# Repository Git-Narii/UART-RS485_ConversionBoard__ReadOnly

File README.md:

RS485からUARTに信号を変換するための基板

逆方向の変換は不可

双方向化Ver.  と通信方向自動制御Ver.は作成中

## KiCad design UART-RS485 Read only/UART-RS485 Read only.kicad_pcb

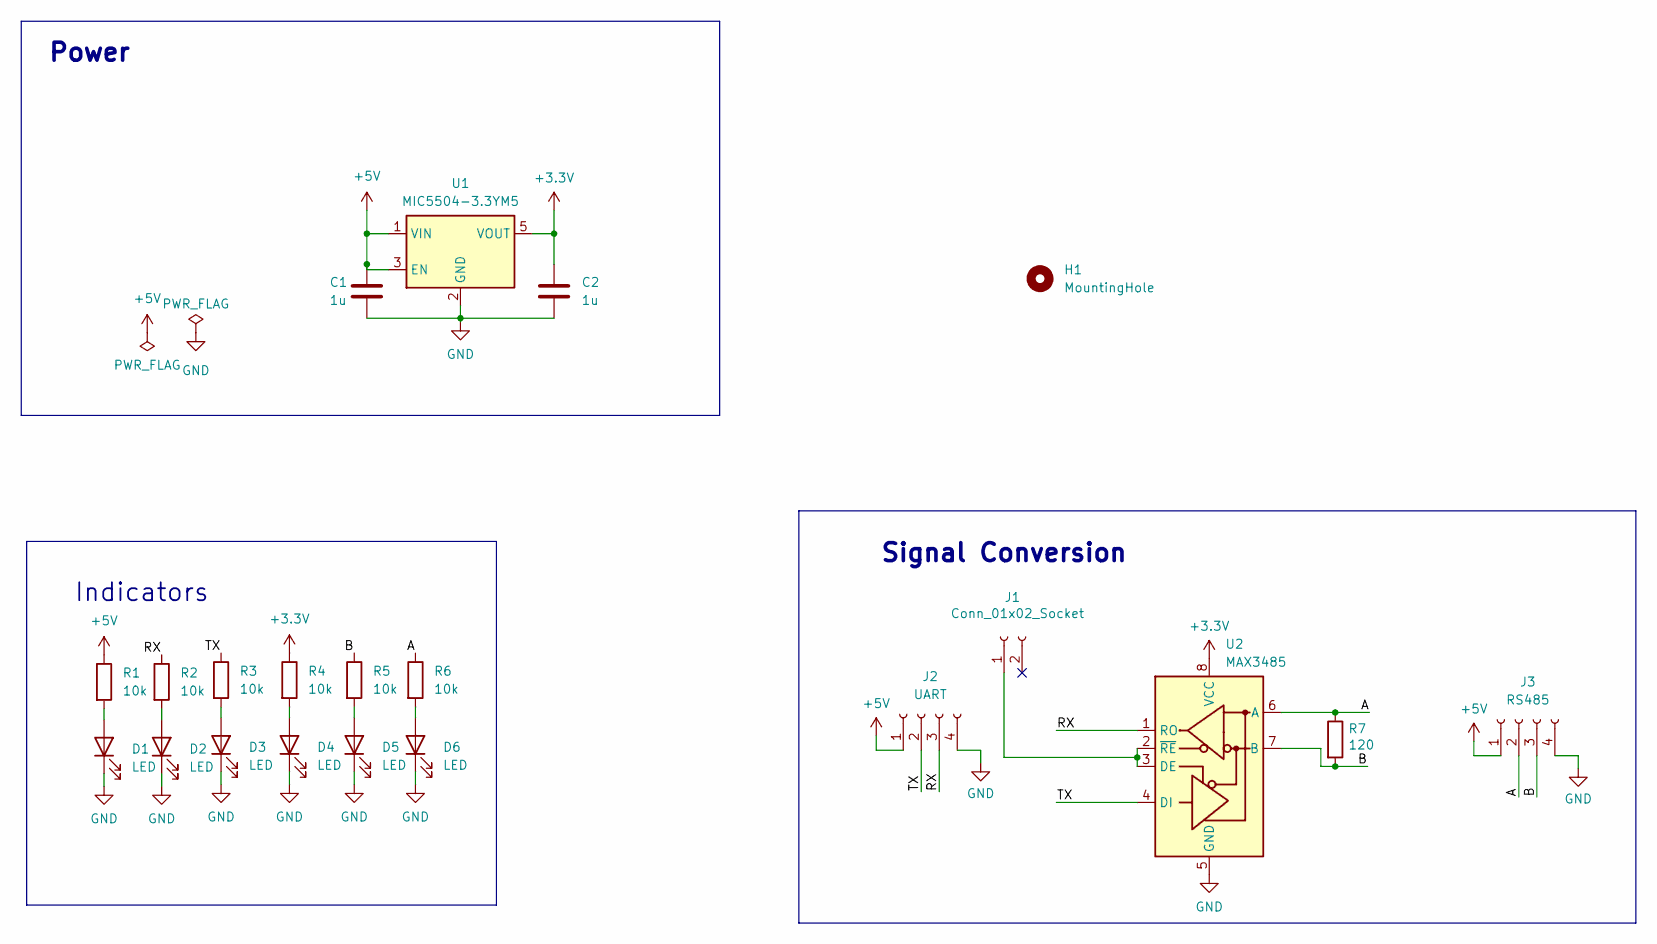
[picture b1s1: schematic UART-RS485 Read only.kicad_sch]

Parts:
C1, C2: 1u; C_0603_1608Metric
D1, D2, D3, D4, D5, D6: LED; LED_0603_1608Metric
H1: MountingHole; MountingHole_3.2mm_M3
J1: Conn_01x02_Socket; JST_XA_S02B-XASK-1_1x02_P2.50mm_Horizontal
J2: UART; JST_XA_S04B-XASK-1_1x04_P2.50mm_Horizontal
J3: RS485; JST_XA_S04B-XASK-1_1x04_P2.50mm_Horizontal
R1, R2, R3, R4, R5, R6: 10k; R_0603_1608Metric
R7: 120; R_0603_1608Metric
U1: MIC5504-3.3YM5; SOT-23-5
U2: MAX3485; SOIC-8_3.9x4.9mm_P1.27mm

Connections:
+3.3V: C2.1, R4.1, U1.5 (VOUT), U2.8 (VCC)
+5V: C1.1, J2.1, J3.1, R1.1, U1.1 (VIN), U1.3 (EN)
/A: J3.2, R6.1, R7.1, U2.6 (A)
/B: J3.3, R5.1, R7.2, U2.7 (B)
/RX: J2.3, R2.1, U2.1 (RO)
/TX: J2.2, R3.1, U2.4 (DI)
GND: C1.2, C2.2, D1.1 (K), D2.1 (K), D3.1 (K), D4.1 (K), D5.1 (K), D6.1 (K), J2.4, J3.4, U1.2 (GND), U2.5 (GND)
unnamed: D1.2 (A), R1.2
unnamed: D2.2 (A), R2.2
unnamed: D3.2 (A), R3.2
unnamed: D4.2 (A), R4.2
unnamed: D5.2 (A), R5.2
unnamed: D6.2 (A), R6.2
unnamed: J1.1, U2.2 (~RE), U2.3 (DE)

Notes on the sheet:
Signal Conversion
Power
Indicators

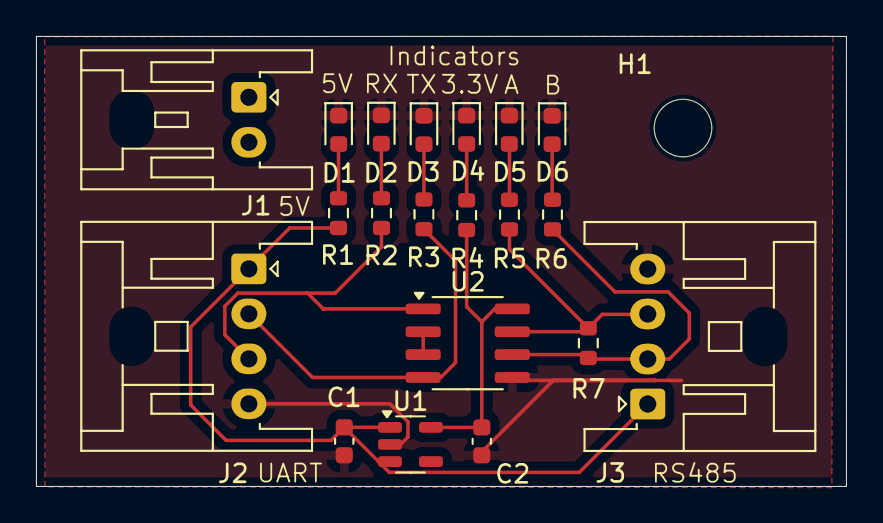
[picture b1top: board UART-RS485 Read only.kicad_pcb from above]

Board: 2 copper layers, 45.0 x 25.0 mm, 21 parts (0 on the bottom side), 14 nets.
